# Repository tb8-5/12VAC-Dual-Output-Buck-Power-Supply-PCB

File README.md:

# 12VAC Dual-Output Buck Power Supply PCB

**Status:** Design Complete / Fabrication In Progress  
**Input:** 12 VAC RMS, 60 Hz  
**Outputs:** Fixed 5 V and 3.3 V rails  
**PCB:** 2-layer, 80.15 mm × 34.20 mm, 1.6 mm FR-4  
**Copper:** 35 µm top / 35 µm bottom  
**Revision:** Rev A  
**Design tools:** KiCad 9 and LTspice  

## Overview

This project is a compact AC-to-DC power supply PCB that accepts **12 VAC** and produces two regulated DC outputs: **5 V** and **3.3 V**.

In simple terms, the board performs three jobs:

1. **Converts AC into DC** using a four-diode bridge rectifier.
2. **Smooths the rectified voltage** using a large bulk capacitor.
3. **Efficiently steps the DC voltage down** into separate 5 V and 3.3 V rails using two buck converters.

The project began with a linear-regulator architecture, but thermal calculations showed that too much power would be lost as heat. I redesigned the supply around two switching regulators and carried the design through schematic capture, component selection, footprint verification, PCB layout, routing, BOM preparation, and assembly-position-file generation.

The board has **not yet been fabricated or bench-tested**, so measured voltage, ripple, load-regulation, efficiency, and thermal results are intentionally left pending.

> **Input note:** This PCB is intended for a low-voltage 12 VAC source. It is not designed to connect directly to wall mains.

---

## Design Decision

### Original Linear-Regulator Approach

The first version used an **LM7805** to generate 5 V, followed by a second linear regulator for the 3.3 V rail.

LTspice rectifier simulation placed the filtered raw DC bus near **15.6 V**. At a 5 V, 1 A operating point, the LM7805 alone would dissipate:

```text
PLOSS = (VIN - VOUT) × IOUT

PLOSS = (15.6 V - 5 V) × 1 A
PLOSS = 10.6 W
```

A linear regulator removes excess voltage by turning it into heat. In this case, the regulator would be dissipating more than 10 W while only delivering 5 W to the load.

That made the linear architecture a poor fit for the size and thermal goals of the board.

### Buck-Converter Redesign

The supply was rebuilt around two fixed-output synchronous buck converters connected in parallel to the rectified DC bus:

- **U2 — AP63205WU-7:** fixed 5 V buck converter
- **U3 — AP63203WU-7:** fixed 3.3 V buck converter

A buck converter uses high-frequency switching, an inductor, and capacitors to transfer energy efficiently instead of continuously burning the voltage difference as heat.

The two output stages are **not cascaded**. Both converters receive power directly from `V_Raw`, so the 3.3 V rail does not depend on the 5 V regulator operating first.

---

## Final Architecture

```text
                         12 VAC INPUT
                              │
                              ▼
                 D1-D4: 1N4004 Bridge Rectifier
                              │
                              ▼
                 C1: 1000 µF Bulk Capacitor
                 R1: 10 kΩ Bleeder Resistor
                              │
                              ▼
                         V_RAW DC BUS
                              │
                 ┌────────────┴────────────┐
                 │                         │
                 ▼                         ▼
        5 V BUCK CONVERTER        3.3 V BUCK CONVERTER
            AP63205WU                 AP63203WU
                 │                         │
         C2: 10 µF input            C6: 10 µF input
         C3: 100 nF BST             C7: 100 nF BST
         L1: 4.7 µH                 L2: 3.9 µH
         C4/C5: 2 × 22 µF           C8/C9: 2 × 22 µF
                 │                         │
                 ▼                         ▼
           J2: 5 V / GND              J3: 3.3 V / GND
                 │                         │
             5 V test pad              3V3 test pad
```

Additional test access is provided for **VRAW** and **GND**.

---

## How the Circuit Works

### 1. AC Input and Full-Wave Rectification

`J1` accepts the 12 VAC input.

The four **1N4004** diodes (`D1-D4`) form a full-wave bridge rectifier. During each half-cycle of the AC waveform, a different pair of diodes conducts so that current through the DC side of the circuit always flows in the same direction.

For a 12 VAC RMS source, the unloaded sine-wave peak is approximately:

```text
VPEAK = VRMS × √2
VPEAK = 12 V × √2
VPEAK ≈ 16.97 V
```

The bridge introduces diode losses, so the usable rectified voltage is lower than the ideal peak. The LTspice work for this design produced a filtered raw bus near **15.6 V**.

Because both halves of the 60 Hz input waveform are used, the rectified ripple occurs at approximately **120 Hz**.

### 2. Bulk Filtering and VRAW

`C1` is a **1000 µF electrolytic capacitor** placed across the rectified output.

The bridge charges C1 near the peaks of the AC waveform. Between peaks, C1 supplies energy to the load and helps keep `V_Raw` from falling immediately back toward zero.

A first-order capacitor-ripple relationship is:

```text
ΔV ≈ ILOAD / (FRIPPLE × C)
```

where:

- `ΔV` is the approximate peak-to-peak bus ripple,
- `ILOAD` is the load current drawn from the rectified bus,
- `FRIPPLE` is approximately 120 Hz for 60 Hz full-wave rectification,
- `C` is the bulk capacitance.

`R1`, a **10 kΩ bleeder resistor**, provides a discharge path for the bulk capacitor after input power is removed. At approximately 15.6 V, it draws about **1.6 mA**, and the nominal `R × C` time constant is approximately **10 seconds**.

### 3. 5 V Buck Stage

The upper regulator stage uses `U2`, an **AP63205WU-7**, to generate the fixed 5 V rail.

Its external power-stage components are:

- `C2` — 10 µF local input capacitor
- `C3` — 100 nF bootstrap capacitor
- `L1` — 4.7 µH **TYS60284R7N-10**
- `C4`, `C5` — two 22 µF output capacitors

The switching node drives L1, and the inductor/output-capacitor network filters the switched waveform into a regulated DC output.

The finished 5 V rail is available at:

- `J2`
- the dedicated **5V** test pad

### 4. 3.3 V Buck Stage

The lower stage follows the same architecture using `U3`, an **AP63203WU-7**, for the fixed 3.3 V rail.

Its external components are:

- `C6` — 10 µF local input capacitor
- `C7` — 100 nF bootstrap capacitor
- `L2` — 3.9 µH **ASPI-0628-3R9M-T1**
- `C8`, `C9` — two 22 µF output capacitors

The finished 3.3 V rail is available at:

- `J3`
- the dedicated **3V3** test pad

---

## PCB Implementation

The final layout is a **2-layer board** measuring **80.15 mm × 34.20 mm**.

### Layer Stack

```text
Top Silkscreen
Top Solder Mask
35 µm F.Cu
1.51 mm FR-4 core
35 µm B.Cu
Bottom Solder Mask
Bottom Silkscreen
```

The complete PCB thickness is configured as **1.6 mm**.

### Layout Strategy

The board is organized left-to-right by power flow:

```text
12 VAC Input
    →
Bridge Rectifier
    →
Bulk Filtering / VRAW
    →
Parallel 5 V and 3.3 V Buck Stages
    →
Output Connectors
```

This physical organization makes the circuit easier to follow visually and keeps the functional blocks separated.

Other layout decisions include:

- **All populated assembly components are on the top side.**
- A **GND copper zone covers the bottom copper layer** to provide a low-impedance ground return.
- Wider traces are used on the main power paths, with routed widths reaching **1.25 mm** on portions of `V_Raw`.
- The regulated output routing uses wider sections up to approximately **0.75-1.0 mm**.
- Smaller **0.20 mm** traces are used where appropriate for lower-current local connections.
- The board includes plated test pads for `VRAW`, `5V`, `3V3`, and `GND`.
- The test pads are excluded from pick-and-place output because no separate test-point component needs to be assembled.
- `L1` uses a custom footprint matched to the **TYS60284R7N-10** land pattern.
- `L2` uses the custom **IND_ASPI-0628-3R9M-T1** footprint.
- Front silkscreen labels identify the input, both outputs, ground points, `VRAW`, and **REV A**.

---

## Test and Debug Access

Four dedicated plated test pads are included:

| Test pad | Purpose |
|---|---|
| `VRAW` | Measure the rectified and bulk-filtered DC bus |
| `5V` | Measure the regulated 5 V output |
| `3V3` | Measure the regulated 3.3 V output |
| `GND` | Oscilloscope / multimeter ground reference |

These pads are intended to make bring-up easier with a multimeter or oscilloscope without requiring probes to contact the small regulator pins directly.

---

## Bill of Materials

The current assembly BOM contains **11 unique line items and 21 populated components**:

- **13 SMD components**
- **8 through-hole components**
- **4 additional bare test-point pads** on the PCB

| Ref. | Qty. | Value / Function | Actual Part Number | Vendor Part # | Footprint |
|---|---:|---|---|---|---|
| C1 | 1 | 1000 µF bulk capacitor | `35PK1000MEFC10X20` | `C1580768` | `CP_Radial_D10.0mm_P5.00mm` |
| C2, C6 | 2 | 10 µF buck input capacitors | `CGA1206X5R106K350NT` | `C6119957` | `C_1206_3216Metric` |
| C3, C7 | 2 | 100 nF bootstrap capacitors | `C0603C104K5RACTU` | `C127833` | `C_0603_1608Metric` |
| C4, C5, C8, C9 | 4 | 22 µF output capacitors | `TMK316BBJ226ML-T` | `C386093` | `C_1206_3216Metric` |
| D1-D4 | 4 | 1N4004 bridge-rectifier diodes | `1N4004` | `C3058` | `D_DO-41_SOD81_P10.16mm_Horizontal` |
| J1-J3 | 3 | 2-position 5.0 mm terminal blocks | `MX126-5.0-02P-GN01-Cu-S-A` | `C5188434` | `TerminalBlock_MaiXu_MX126-5.0-02P_1x02_P5.00mm` |
| L1 | 1 | 4.7 µH 5 V buck inductor | `TYS60284R7N-10` | `C2454435` | `L_6.0x6.0_Pad1.8x5.7_Gap2.6` |
| L2 | 1 | 3.9 µH 3.3 V buck inductor | `ASPI-0628-3R9M-T1` | `C7325703` | `IND_ASPI-0628-3R9M-T1` |
| R1 | 1 | 10 kΩ VRAW bleeder resistor | `CRCW120610K0FKEA` | `C242483` | `R_1206_3216Metric` |
| U2 | 1 | Fixed 5 V synchronous buck | `AP63205WU-7` | `C2071056` | `TSOT-23-6` |
| U3 | 1 | Fixed 3.3 V synchronous buck | `AP63203WU-7` | `C780769` | `TSOT-23-6` |

The spreadsheet used for the current assembly quotation is included in the repository under `03_kicad`.

---

## KiCad / Manufacturing Files

The `03_kicad` directory contains the current source and assembly-support files:

```text
03_kicad/
├── screenshots/
├── psu_board.png
├── psu_bom(2026-08-06).xlsx
├── psu_main.kicad_pcb
├── psu_main.kicad_pro
├── psu_main.kicad_sch
├── psu_main-top.pos
└── psu_main-bottom.pos
```

Useful direct links:

- [KiCad schematic](03_kicad/psu_main.kicad_sch)
- [KiCad PCB layout](03_kicad/psu_main.kicad_pcb)
- [KiCad project file](03_kicad/psu_main.kicad_pro)
- [Assembly BOM](03_kicad/psu_bom%282026-08-06%29.xlsx)
- [Top-side component positions](03_kicad/psu_main-top.pos)
- [Bottom-side component positions](03_kicad/psu_main-bottom.pos)

The top-side position file contains all 21 populated BOM components. The bottom-side position file is intentionally empty because no assembly components are mounted on the bottom of the PCB.

---

## Current Validation Status

### Completed

- Initial linear-regulator thermal analysis
- LTspice bridge-rectifier / bulk-filter simulation
- Buck-converter architecture redesign
- Component selection
- Schematic capture
- Footprint assignment and verification
- Custom inductor footprint integration
- 2-layer PCB placement and routing
- Bottom-layer GND plane
- Input / output / VRAW test access
- BOM generation and assembly part matching
- Top and bottom component-position-file generation
- Fabrication package review

### Pending - Board Review

The board has not yet been physically validated. Bench testing will include:

1. Visual inspection and continuity checks before power-up
2. `VRAW` DC level and 120 Hz ripple measurement
3. 5 V output-voltage verification
4. 3.3 V output-voltage verification
5. Output ripple measurement with an oscilloscope
6. Load-regulation testing
7. Regulator and inductor thermal checks under load
8. Comparison of measured results against the calculated and simulated behavior

No measured hardware results are reported in this repository until the fabricated board has been assembled and tested.

---

## Project Goal

The goal of this project was not only to create two DC rails, but to work through the complete hardware-design process:

```text
Requirements
    →
Architecture Selection
    →
Calculation / Simulation
    →
Component Selection
    →
Schematic Capture
    →
Footprint Verification
    →
PCB Layout and Routing
    →
Manufacturing Documentation
    →
Fabrication
    →
Bench Validation
```

The largest design change came from recognizing that the original linear-regulator architecture created an unacceptable thermal problem and then redesigning the system around switching regulators before committing the PCB to fabrication.

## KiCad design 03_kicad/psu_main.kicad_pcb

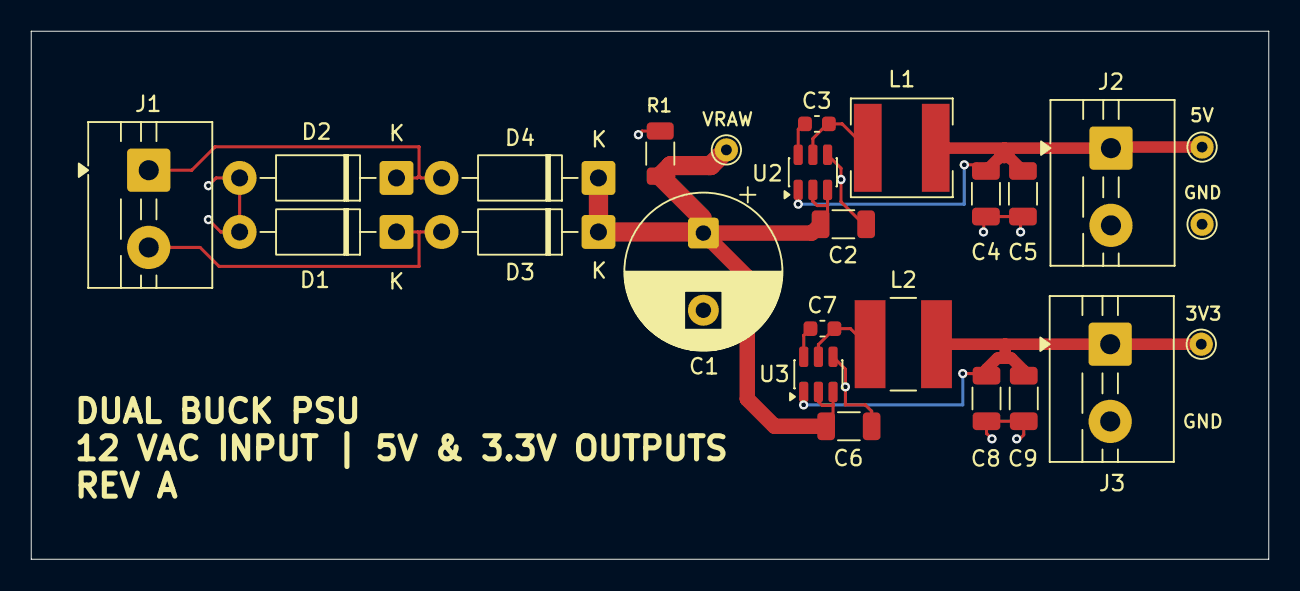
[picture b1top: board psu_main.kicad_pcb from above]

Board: 2 copper layers, 80.2 x 34.2 mm, 25 parts (0 on the bottom side), 10 nets.

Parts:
3V3: 3V3_Out; TestPoint_THTPad_D1.5mm_Drill0.7mm
5V: 5V_Out; TestPoint_THTPad_D1.5mm_Drill0.7mm
C1: 1000uF; CP_Radial_D10.0mm_P5.00mm
C2, C6: 10uF; C_1206_3216Metric
C3, C7: 100nF; C_0603_1608Metric
C4, C5, C8, C9: 22uF; C_1206_3216Metric
D1, D2, D3, D4: 1N4004; D_DO-41_SOD81_P10.16mm_Horizontal
GND: TestPoint; TestPoint_THTPad_D1.5mm_Drill0.7mm
J1: 12VAC IN; TerminalBlock_MaiXu_MX126-5.0-02P_1x02_P5.00mm
J2: 5V_Out; TerminalBlock_MaiXu_MX126-5.0-02P_1x02_P5.00mm
J3: 3V3_Out; TerminalBlock_MaiXu_MX126-5.0-02P_1x02_P5.00mm
L1: 4.7uH; L_6.0x6.0_Pad1.8x5.7_Gap2.6
L2: 3.9uH; IND_ASPI-0628-3R9M-T1
R1: 10k; R_1206_3216Metric
U2: AP63205WU; TSOT-23-6
U3: AP63203WU; TSOT-23-6
VRAW: TestPoint; TestPoint_THTPad_D1.5mm_Drill0.7mm

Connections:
/3V3_Out: 3V3.1, C8.1, C9.1, J3.1, L2.2, U3.1 (FB)
/5V_Out: 5V.1, C4.1, C5.1, J2.1, L1.2, U2.1 (FB)
/V_Raw: C1.1, C2.1, C6.1, D3.1 (K), D4.1 (K), R1.1, U2.2 (EN), U2.3 (IN), U3.2 (EN), U3.3 (IN), VRAW.1
GND: C1.2, C2.2, C4.2, C5.2, C6.2, C8.2, C9.2, D1.2 (A), D2.2 (A), GND.1, J2.2, J3.2, R1.2, U2.4 (GND), U3.4 (GND)
unnamed: D1.1 (K), D3.2 (A), J1.2
unnamed: D2.1 (K), D4.2 (A), J1.1
unnamed: C3.2, U2.6 (BST)
unnamed: C3.1, L1.1, U2.5 (SW)
unnamed: C7.2, U3.6 (BST)
unnamed: C7.1, L2.1, U3.5 (SW)

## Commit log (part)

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2026-06-07 Adding planned design and LTspice simulations
2026-06-07 Revise README with project details and status
    Updated project overview, goals, current status, simulation details, and planned features for the custom PSU PCB and analog characterization platform.
